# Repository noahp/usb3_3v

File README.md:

usb3_3v
=====

USB to 3.3v regulator.

Parts
=====
http://www.mouser.com/ProductDetail/Micrel/MIC5504-33YM5-TR/?qs=sGAEpiMZZMsGz1a6aV8DcH%252bs3fyc%252bB46uPJfIpoBEn4%3d

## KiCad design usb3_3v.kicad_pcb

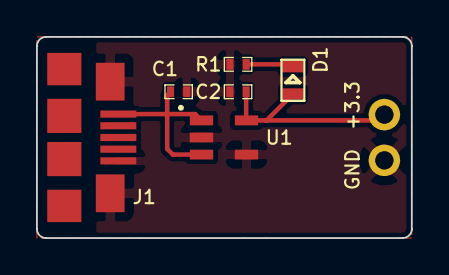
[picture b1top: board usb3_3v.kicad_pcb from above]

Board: 2 copper layers, 20.8 x 11.2 mm, 8 parts (0 on the bottom side), 4 nets.

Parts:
C1, C2: 1uF; SM0402_c
D1: LED; SM0603
J1: USB-MICRO-B; usb_micro_b_smt
P1: +3.3; TEST_0.100
P2: GND; TEST_0.100
R1: 1K; SM0402_r
U1: AAT3221 / MIC5504; sot23-5_noah

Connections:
/+3.3v: C2.1, D1.1, P1.1, U1.5
/+5v: C1.1, J1.1, U1.1, U1.3
GND: C1.2, C2.2, J1.5, J1.6, P2.1, R1.2, U1.2, U1.4
unnamed: D1.2, R1.1

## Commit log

2014-09-16 - add kicadlib
2014-09-16 - basic schematic, save it
2014-09-16 - add net list
2014-09-16 - save pcb
2014-09-16 - pcb done, add gerbers
2014-09-16 - fix gerbers
2014-09-17 - clean up silks a bit
2014-09-17 - add render
